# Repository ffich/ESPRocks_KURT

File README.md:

# ⚡🐢 ESPRocks KURT — Solder-Free ESP32 Development Board  

# ESPRocks
ESPRocks are Open Source development boards that I designed in collaborartion with [Vincenzo Cacciatore](https://github.com/caccia78). They are based on ESP32 modules designed to help DIY developers to create reliable and flexible home automation systems with ease - with no soldering.

---

## 📖 What is KURT?  

KURT is a **versatile ESP32 development board** that’s:  
- 🧠 **Smart** — Powered by the dual-core Wi-Fi + Bluetooth ESP32 SoC  
- 🔌 **Modular** — Adapter slots for sensors, displays, relays, LEDs, and more  
- 🛡 **Safe** — Foolproof keyed connectors prevent wiring mistakes  
- 🏎 **Fast** — No soldering, no breadboard spaghetti — just plug & play

Fig.1 - Kurt Board

Fig.2 - Adapters

---

## 📦 What’s in the Kit?  

| Icon | Item | Description |
|------|------|-------------|
| 🐢 | **KURT Board (ESP32)** | The heart of the system — ready for Wi-Fi & Bluetooth projects |
| 🔌 | **4× Adapters** | Connect peripherals in seconds |
| 🪢 | **JST-PH 2.0 Cables** | Secure, tidy wiring |
| 💡 | **Example Peripherals** | Works with buttons, PIRs, OLEDs, relays, WS2812b LEDs & more |

---

## 🚀 Why KURT Rocks  

- 🛠 **No soldering** — Perfect for beginners & fast prototyping  
- 🎯 **Error-proof connectors** — Avoid reversed or wrong wiring  
- ⚡ **Selectable power outputs** — Switch between 3.3 V & 5 V peripherals  
- 🔄 **Hot-swap ready** — Swap modules without rewiring your entire setup  
- 🏠 **IoT-friendly** — Works great with ESPHome & Home Assistant  
- 📖 **Clear labeling** — Easy pinout reading without datasheets  
- 🧹 **Tidy builds** — No messy jumper wires

---

## 🎯 Ideal For  

- 👩‍🔧 Makers & hobbyists who want quick results  
- 🧑‍🏫 Educators teaching IoT & embedded systems  
- 🏠 Smart home DIY projects  
- 🎨 Creative prototypes for events & exhibitions  

---

## 🌐 Try the KURT Configurator  

🔗 **[KURT Online Configurator](https://www.esprocks.it/kurt/configurator)** — Explore supported modules, plan your setup, and get assembly tips with an interactive tool.  

---

## 📂 What’s in This Repo?  

This is the **hardware repository** for KURT:  
- 🗺 **Schematics**  
- 🖼 **PCB layouts**  
- 📋 **BOM** (Bill of Materials)  
- 🖌 **3D models**  

---

## 🏆 Summary  

🐢 **ESPRocks KURT** makes ESP32 prototyping **fun, fast, and frustration-free**.  
Whether you’re building a smart lamp, an interactive art piece, or a home automation sensor — KURT gets you there **without soldering a single wire**.  

---

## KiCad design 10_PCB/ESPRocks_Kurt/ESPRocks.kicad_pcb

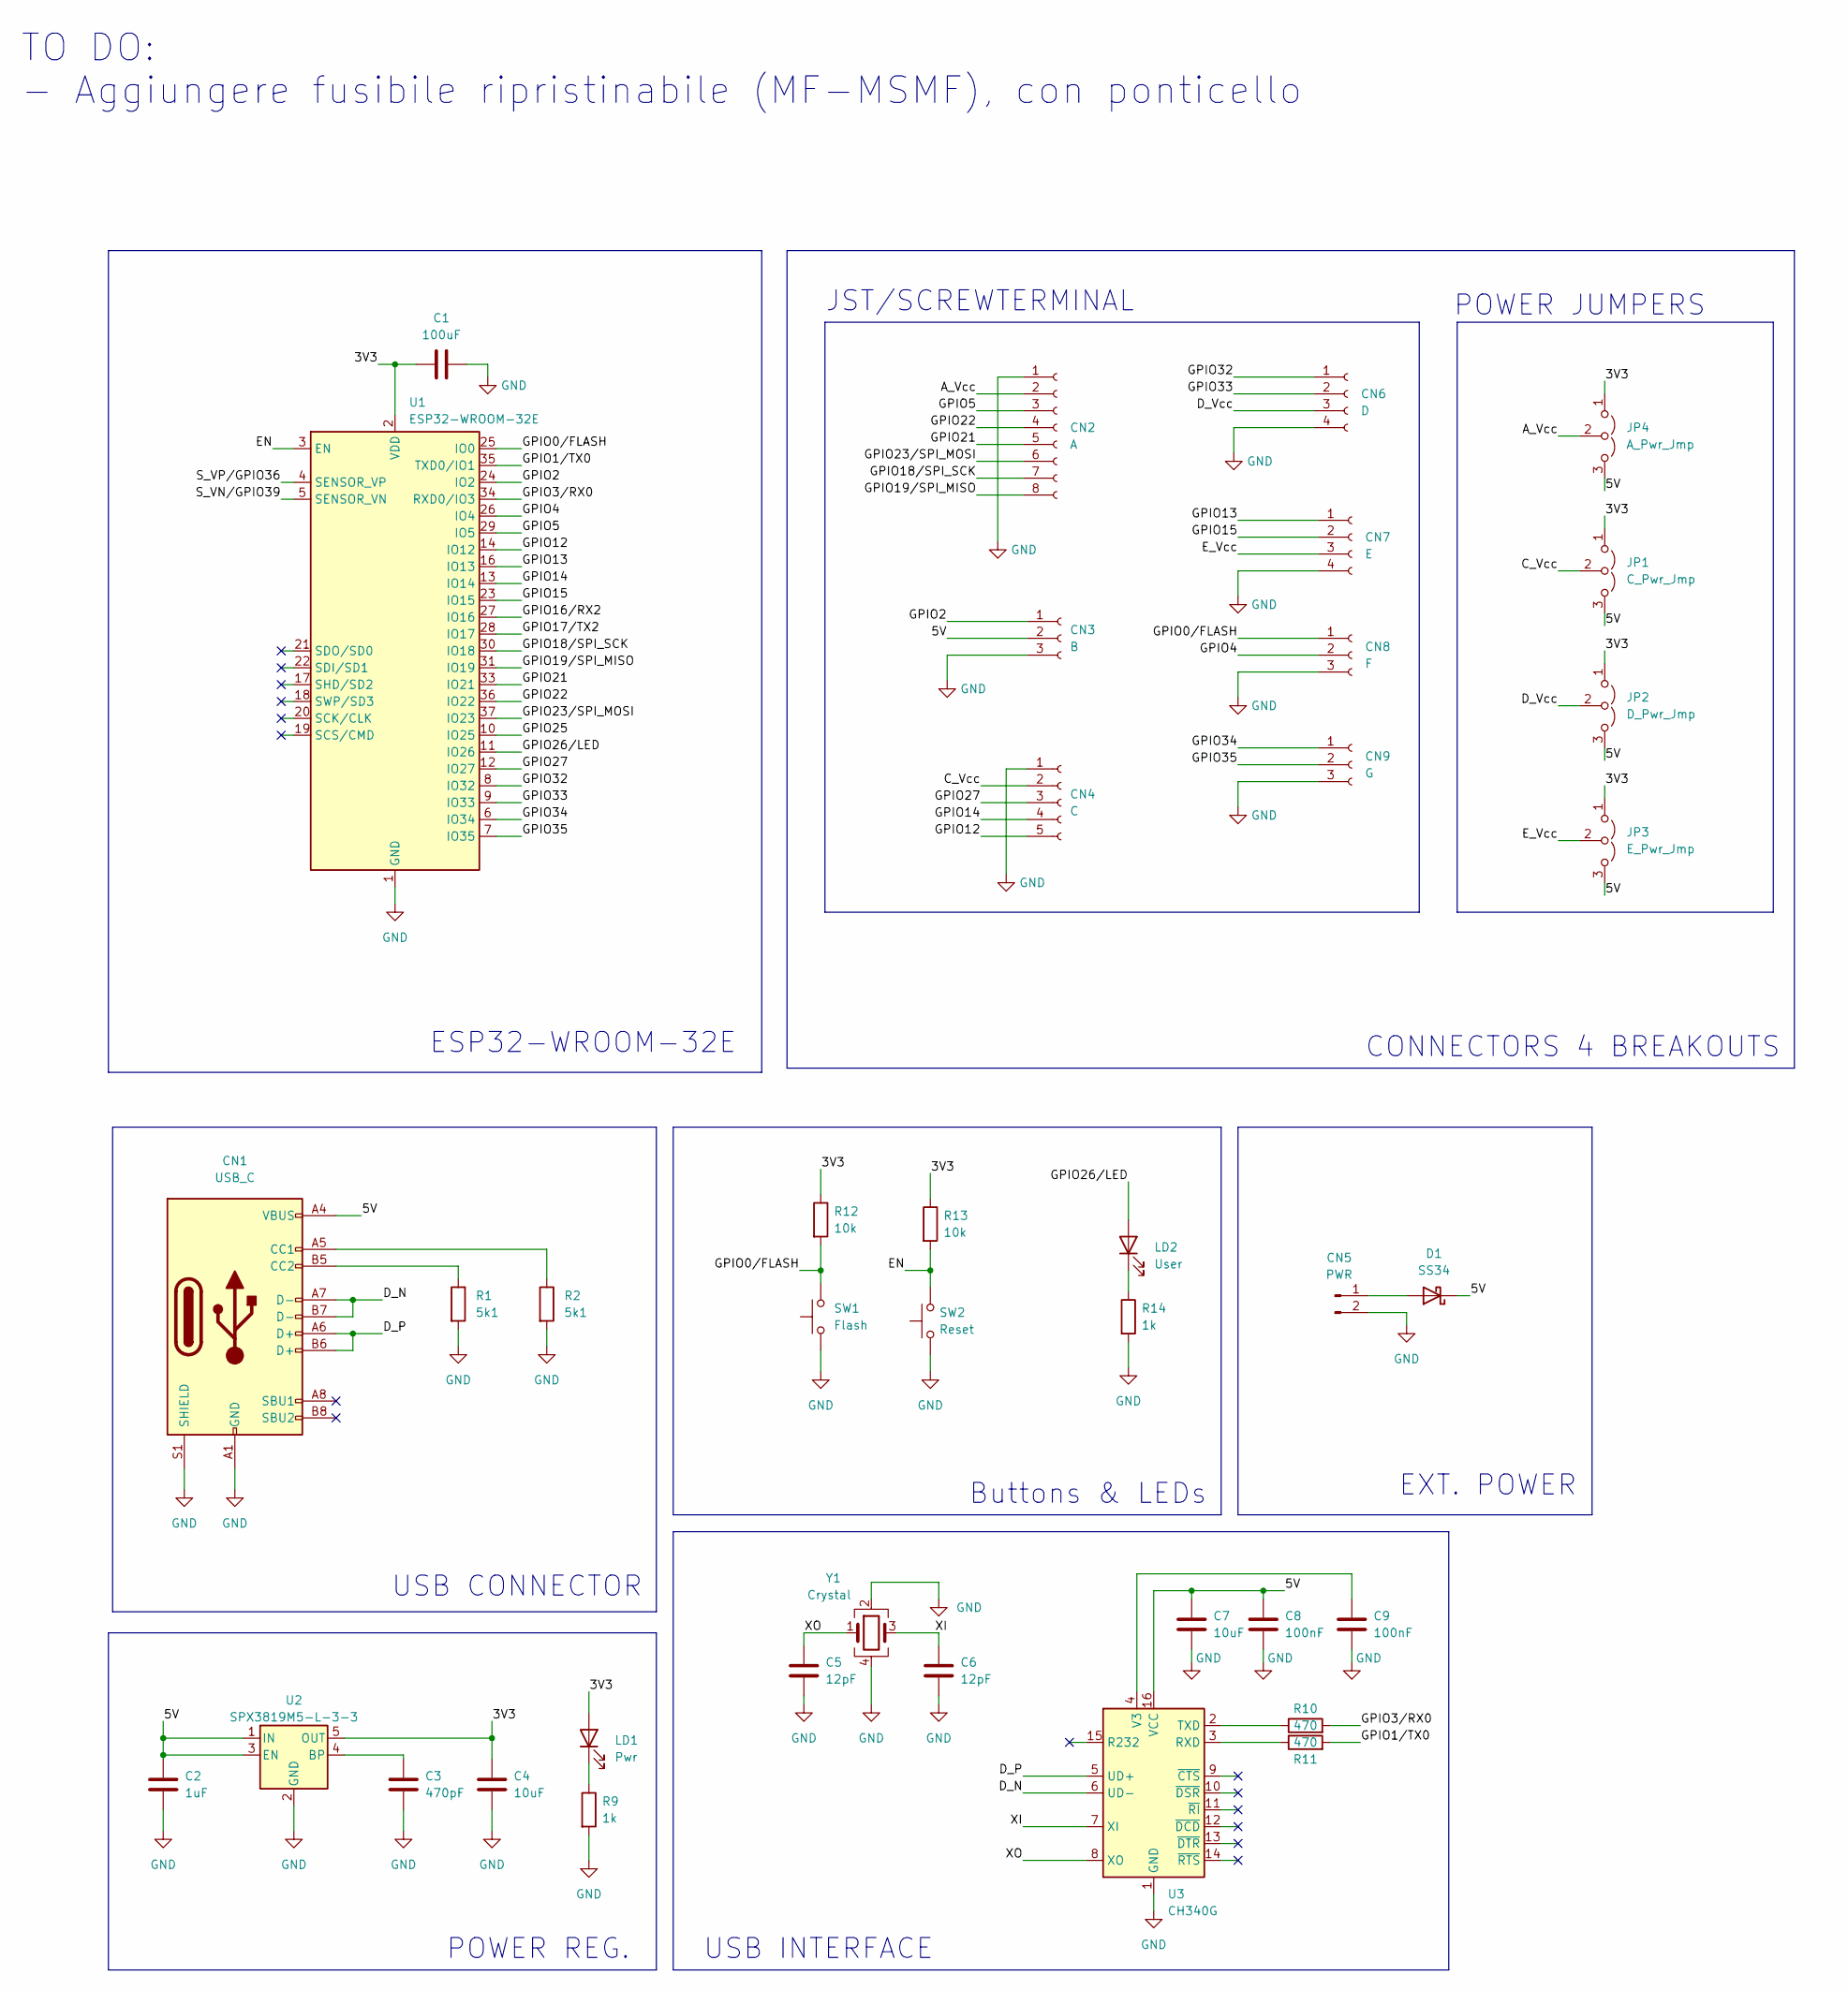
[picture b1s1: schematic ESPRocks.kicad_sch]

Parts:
C1: 100uF; C_1206_3216Metric; LCSC C15008
C2: 1uF; C_0402_1005Metric; LCSC C52923
C3: 470pF; C_0402_1005Metric; LCSC C1537
C4, C7: 10uF; C_0402_1005Metric; LCSC C15525
C5, C6: 12pF; C_0402_1005Metric; LCSC C1547
C8, C9: 100nF; C_0402_1005Metric; LCSC C1525
CN1: USB_C; USB_C_Receptacle_HRO_TYPE-C-31-M-12; LCSC C165948
CN2: A; JST_PH_B8B-PH-K_1x08_P2.00mm_Vertical; LCSC C157974
CN3: B; TerminalBlock_Phoenix_MKDS-1,5-3-5.08_1x03_P5.08mm_Horizont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; LCSC C72334
CN4: C; JST_PH_B5B-PH-K_1x05_P2.00mm_Vertical; LCSC C157993
CN5: PWR; TerminalBlock_Phoenix_MKDS-1,5-2-5.08_1x02_P5.08mm_Horizont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; LCSC C8465
CN6: D; JST_PH_B4B-PH-K_1x04_P2.00mm_Vertical; LCSC C131334
CN7: E; JST_PH_B4B-PH-K_1x04_P2.00mm_Vertical; LCSC C131334
CN8: F; TerminalBlock_Phoenix_MKDS-1,5-3-5.08_1x03_P5.08mm_Horizont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; LCSC C72334
CN9: G; TerminalBlock_Phoenix_MKDS-1,5-3-5.08_1x03_P5.08mm_Horizont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; LCSC C72334
D1: SS34; D_SMA; LCSC C8678
JP1: C_Pwr_Jmp; PinHeader_1x03_P2.54mm_Vertical; LCSC C390679
JP2: D_Pwr_Jmp; PinHeader_1x03_P2.54mm_Vertical; LCSC C390679
JP3: E_Pwr_Jmp; PinHeader_1x03_P2.54mm_Vertical; LCSC C390679
JP4: A_Pwr_Jmp; PinHeader_1x03_P2.54mm_Vertical; LCSC C390679
LD1: Pwr; LED_0603_1608Metric; LCSC C2286
LD2: User; LED_0603_1608Metric; LCSC C2288
R1, R2: 5k1; R_0402_1005Metric; LCSC C25905
R9, R14: 1k; R_0402_1005Metric; LCSC C11702
R10, R11: 470; R_0402_1005Metric; LCSC C25117
R12, R13: 10k; R_0402_1005Metric; LCSC C25744
SW1: Flash; SW_Push_1P1T_NO_6x6mm_H9.5mm; LCSC C127509
SW2: Reset; SW_Push_1P1T_NO_6x6mm_H9.5mm; LCSC C127509
U1: ESP32-WROOM-32E; ESP32-WROOM-32; LCSC C701342
U2: SPX3819M5-L-3-3; SOT-23-5; LCSC C9055
U3: CH340G; SOIC-16_3.9x9.9mm_P1.27mm; LCSC C14267
Y1: Crystal; Crystal_SMD_3225-4Pin_3.2x2.5mm; LCSC C9002

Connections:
/3V3: C1.1, C4.1, JP1.1 (A), JP2.1 (A), JP3.1 (A), JP4.1 (A), LD1.2 (A), R12.1, R13.1, U1.2 (VDD), U2.5 (OUT)
/5V: C2.1, C7.1, C8.1, CN1.A4 (VBUS), CN1.A9 (VBUS), CN1.B4 (VBUS), CN1.B9 (VBUS), CN3.2, D1.1 (K), JP1.3 (B), JP2.3 (B), JP3.3 (B), JP4.3 (B), U2.1 (IN), U2.3 (EN), U3.16 (VCC)
/A_Vcc: CN2.2, JP4.2 (C)
/C_Vcc: CN4.2, JP1.2 (C)
/D_N: CN1.A7 (D-), CN1.B7 (D-), U3.6 (UD-)
/D_P: CN1.A6 (D+), CN1.B6 (D+), U3.5 (UD+)
/D_Vcc: CN6.3, JP2.2 (C)
/EN: R13.2, SW2.2, U1.3 (EN)
/E_Vcc: CN7.3, JP3.2 (C)
/GPIO0/FLASH: CN8.1, R12.2, SW1.2, U1.25 (IO0)
/GPIO1/TX0: R11.2, U1.35 (TXD0/IO1)
/GPIO2: CN3.1, U1.24 (IO2)
/GPIO3/RX0: R10.2, U1.34 (RXD0/IO3)
/GPIO4: CN8.2, U1.26 (IO4)
/GPIO5: CN2.3, U1.29 (IO5)
/GPIO12: CN4.5, U1.14 (IO12)
/GPIO13: CN7.1, U1.16 (IO13)
/GPIO14: CN4.4, U1.13 (IO14)
/GPIO15: CN7.2, U1.23 (IO15)
/GPIO16/RX2: U1.27 (IO16)
/GPIO17/TX2: U1.28 (IO17)
/GPIO18/SPI_SCK: CN2.7, U1.30 (IO18)
/GPIO19/SPI_MISO: CN2.8, U1.31 (IO19)
/GPIO21: CN2.5, U1.33 (IO21)
/GPIO22: CN2.4, U1.36 (IO22)
/GPIO23/SPI_MOSI: CN2.6, U1.37 (IO23)
/GPIO25: U1.10 (IO25)
/GPIO26/LED: LD2.2 (A), U1.11 (IO26)
/GPIO27: CN4.3, U1.12 (IO27)
/GPIO32: CN6.1, U1.8 (IO32)
/GPIO33: CN6.2, U1.9 (IO33)
/GPIO34: CN9.1, U1.6 (IO34)
/GPIO35: CN9.2, U1.7 (IO35)
/S_VN/GPIO39: U1.5 (SENSOR_VN)
/S_VP/GPIO36: U1.4 (SENSOR_VP)
/XI: C6.1, U3.7 (XI), Y1.3
/XO: C5.1, U3.8 (XO), Y1.1
GND: C1.2, C2.2, C3.2, C4.2, C5.2, C6.2, C7.2, C8.2, C9.2, CN1.A1 (GND), CN1.A12 (GND), CN1.B1 (GND), CN1.B12 (GND), CN1.S1 (SHIELD), CN2.1, CN3.3, CN4.1, CN5.2, CN6.4, CN7.4, CN8.3, CN9.3, R1.2, R2.2, R9.2, R14.2, SW1.1, SW2.1, U1.1 (GND), U1.15 (GND), U1.38 (GND), U1.39 (GND), U2.2 (GND), U3.1 (GND), Y1.2, Y1.4
unnamed: C3.1, U2.4 (BP)
unnamed: C9.1, U3.4 (V3)
unnamed: CN1.A5 (CC1), R2.1
unnamed: CN1.B5 (CC2), R1.1
unnamed: CN5.1, D1.2 (A)
unnamed: LD1.1 (K), R9.1
unnamed: LD2.1 (K), R14.1
unnamed: R10.1, U3.2 (TXD)
unnamed: R11.1, U3.3 (RXD)

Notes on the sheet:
TO DO: - Aggiungere fusibile ripristinabile (MF-MSMF), con ponticello
ESP32-WROOM-32E
Buttons & LEDs
POWER REG.
POWER JUMPERS
USB CONNECTOR
EXT. POWER
USB INTERFACE
JST/SCREWTERMINAL
CONNECTORS 4 BREAKOUTS

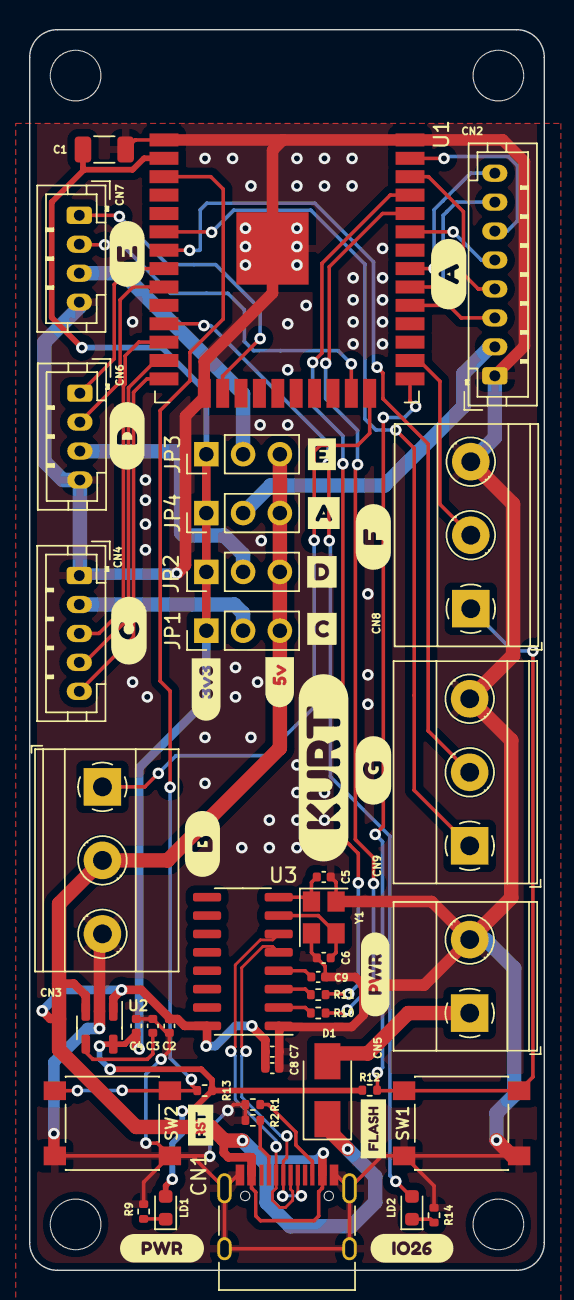
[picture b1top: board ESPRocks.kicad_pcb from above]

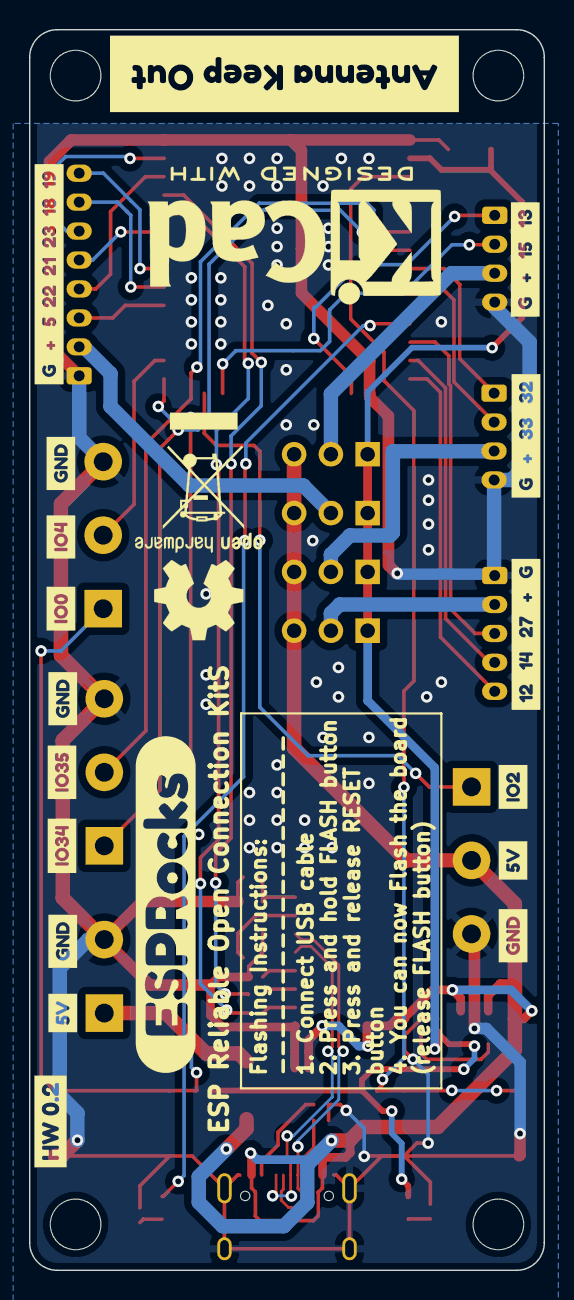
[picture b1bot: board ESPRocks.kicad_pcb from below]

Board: 2 copper layers, 35.6 x 85.7 mm, 76 parts (18 on the bottom side), 42 nets.

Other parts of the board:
kibuzzard-633DE5EA: G***; kibuzzard-633DE5EA
kibuzzard-633DE5F9: G***; kibuzzard-633DE5F9
kibuzzard-633DE20B: G***; kibuzzard-633DE20B
kibuzzard-633DE216: G***; kibuzzard-633DE216
kibuzzard-633DE730: G***; kibuzzard-633DE730
kibuzzard-633DEAE8: G***; kibuzzard-633DEAE8
kibuzzard-633DEAFD: G***; kibuzzard-633DEAFD
kibuzzard-633DEB42, kibuzzard-633DEB42#2: G***; kibuzzard-633DEB42
kibuzzard-633DEB59, kibuzzard-633DEB59#2, kibuzzard-633DEB59#3, kibuzzard-633DEB59#4: G***; kibuzzard-633DEB59
kibuzzard-633DEB90: G***; kibuzzard-633DEB90
kibuzzard-633DEFBF: G***; kibuzzard-633DEFBF
kibuzzard-633DEFCA: G***; kibuzzard-633DEFCA
kibuzzard-633DEFD9: G***; kibuzzard-633DEFD9
kibuzzard-633DEFE5: G***; kibuzzard-633DEFE5
kibuzzard-633F126E: G***; kibuzzard-633F126E
kibuzzard-633F140C: G***; kibuzzard-633F140C
kibuzzard-633F1259: G***; kibuzzard-633F1259
kibuzzard-633F1449: G***; kibuzzard-633F1449
kibuzzard-635D64EE: G***; kibuzzard-635D64EE
kibuzzard-635D654D: G***; kibuzzard-635D654D
kibuzzard-6341AAF6: G***; kibuzzard-6341AAF6
kibuzzard-6341BAB6: G***; kibuzzard-6341BAB6
kibuzzard-6341BAF6: G***; kibuzzard-6341BAF6
kibuzzard-6341BB0D: G***; kibuzzard-6341BB0D
kibuzzard-6341BB74: G***; kibuzzard-6341BB74
kibuzzard-62924A8F, kibuzzard-62924A8F#2: G***; kibuzzard-62924A8F
kibuzzard-63307F6C: G***; kibuzzard-63307F6C
kibuzzard-63307FA1: G***; kibuzzard-63307FA1
kibuzzard-63307FB0: G***; kibuzzard-63307FB0
kibuzzard-63307FC4: G***; kibuzzard-63307FC4
kibuzzard-63307FD4: G***; kibuzzard-63307FD4
kibuzzard-633080E5: G***; kibuzzard-633080E5

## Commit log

2023-11-14 ESPRocks KURT and Adapters
2024-11-24 Create LICENSE
    added MIT License
2025-08-12 Update README.md
    updated description
